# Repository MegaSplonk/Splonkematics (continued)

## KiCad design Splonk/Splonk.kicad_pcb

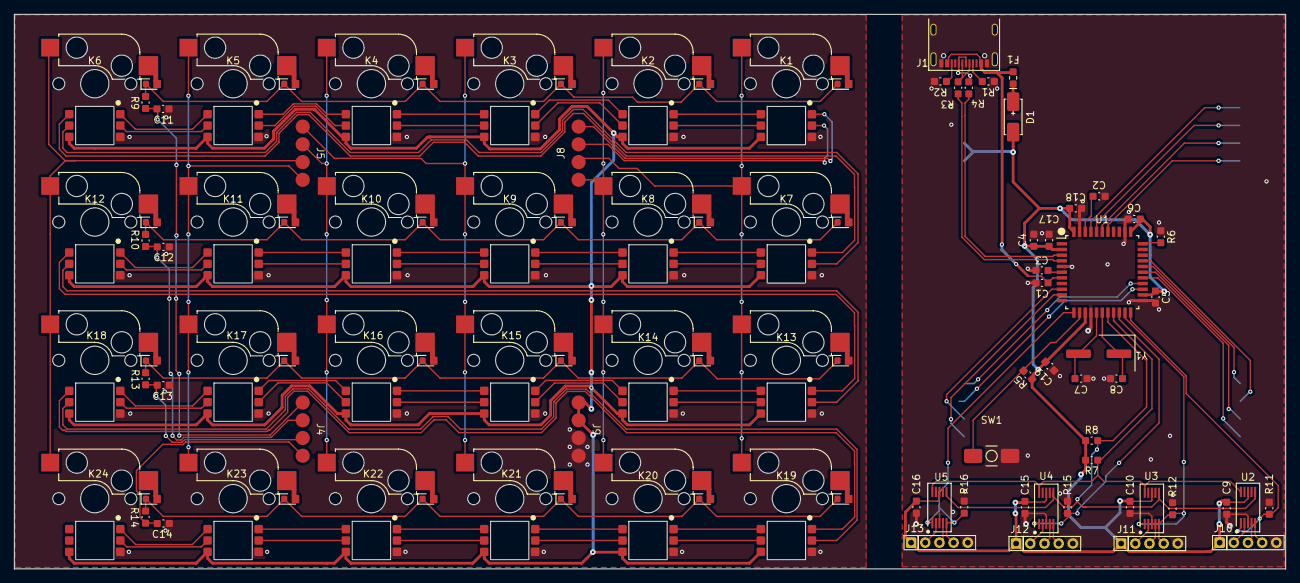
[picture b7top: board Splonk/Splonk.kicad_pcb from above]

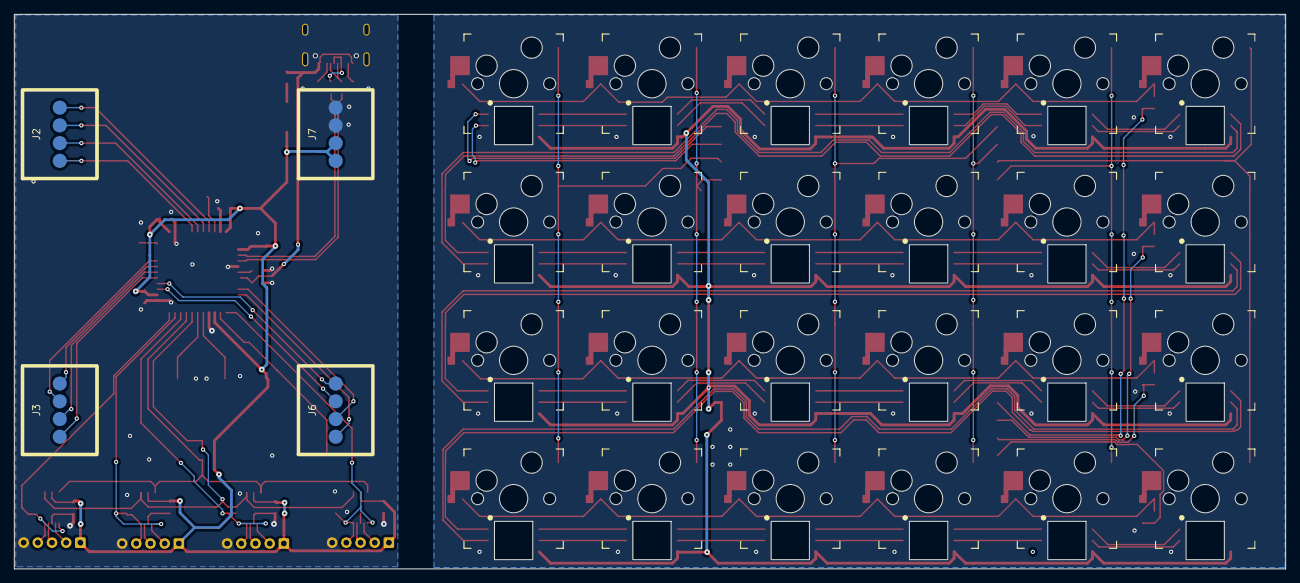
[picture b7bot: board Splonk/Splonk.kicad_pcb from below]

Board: 2 copper layers, 179.2 x 78.2 mm, 81 parts (4 on the bottom side), 104 nets.

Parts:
C1, C3, C4: 1uF; Capacitor_0603
C2, C5, C9, C10, C15, C16, C17, C18, C19: 100nF; Capacitor_0603
C6, C11, C12, C13, C14: 10uF; Capacitor_0603
C7, C8: 27pF; Capacitor_0603
D1: Diode_Schottky; Schottky
F1: PolyFuse; Diode_0603
J1: USB_C_Receptacle_USB2.0_14P; USB-C
J2, J3, J6, J7: POGO; Pogo_4_pin
J4, J5, J8, J9: POGO; Pogo_4_pin_female
J10, J11, J12, J13: SplonkConn; MaixCon-5P
K1, K2, K3, K4, K5, K6, K7, K8, K9, K10, K11, K12, K13, K14, K15, K16, K17, K18, K19, K20, K21, K22, K23, K24: APA102; Kailh_socket_MX_APA102_combo
R1, R2, R3, R4: 5.1K; Resistor_0603
R5, R6, R9, R10, R11, R12, R13, R14, R15, R16: 10K; Resistor_0603
R7, R8: 4.7K; Resistor_0603
SW1: SW_Reset; SMD_Button
U1: ATmega32U4-A; TQFP-44_10x10_Pitch0.8mm
U2, U3, U4, U5: TS5A23157; MSOP-10
Y1: 16MHz; Quatz_16Mhz

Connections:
/logic/AREF: C2.1, U1.42 (AREF)
/logic/BUS_ENABLE^{1}: J10.4, R11.1, U1.22 (PD5/XCK/~CTS), U2.1, U2.5
/logic/BUS_ENABLE^{2}: J11.4, R12.1, U1.21 (PD3/TXD1), U3.1, U3.5
/logic/BUS_ENABLE^{3}: J12.4, R15.1, U1.20 (PD2/RXD1), U4.1, U4.5
/logic/BUS_ENABLE^{4}: J13.4, R16.1, U1.12 (PB7/OC0A/OC1C/~RTS), U5.1, U5.5
/logic/COL^{1}: J6.3, U1.25 (PD4/ICP1/ADC8)
/logic/COL^{2}: J6.4, U1.26 (PD6/T1/~OC4D/ADC9)
/logic/COL^{3}: J3.1, U1.27 (PD7/T2/OC4D/ADC10)
/logic/COL^{4}: J3.2, U1.28 (PB4/ADC11)
/logic/COL^{5}: J3.4, U1.29 (PB5/ADC12/OC1A/~OC4B)
/logic/COL^{6}: J3.3, U1.30 (PB6/ADC13/OC1B/OC4B)
/logic/D+: R4.2, U1.3 (D^{+})
/logic/D-: R3.2, U1.4 (D^{-})
/logic/MOSI: J6.1, U1.10 (PB2/MOSI)
/logic/ROW^{1}: J2.1, U1.38 (PF5/ADC5)
/logic/ROW^{2}: J2.2, U1.39 (PF4/ADC4)
/logic/ROW^{3}: J2.3, U1.40 (PF1/ADC1)
/logic/ROW^{4}: J2.4, U1.41 (PF0/ADC0)
/logic/SCL: R8.2, U1.18 (PD0/OC0B/SCL), U2.6, U3.6, U4.6, U5.6
/logic/SCLK: J6.2, U1.9 (PB1/SCLK)
/logic/SDA: R7.2, U1.19 (PD1/SDA), U2.10, U3.10, U4.10, U5.10
/logic/UCAP: C3.1, U1.6 (UCap)
/logic/VUSB: C1.1, F1.1, J1.A4 (VBUS), J1.B4 (VBUS), U1.7 (VBus)
/logic/~HWB: R6.2, U1.33 (PE2/~HWB)
/logic/~RST: R5.2, SW1.1, U1.13 (~RESET)
/matrix/COL_1: J8.2, K1.7, K7.7, K13.7, K19.7
/matrix/COL_2: J8.1, K2.7, K8.7, K14.7, K20.7
/matrix/COL_3: J5.1, K3.7, K9.7, K15.7, K21.7
/matrix/COL_4: J5.2, K4.7, K10.7, K16.7, K22.7
/matrix/COL_5: J5.4, K5.7, K11.7, K17.7, K23.7
/matrix/COL_6: J5.3, K6.7, K12.7, K18.7, K24.7
/matrix/MOSI: J8.4, K1.1 (D^{in})
/matrix/R1: K1.8, K2.8, K3.8, K4.8, K5.8, K6.8, R9.1
/matrix/R2: K7.8, K8.8, K9.8, K10.8, K11.8, K12.8, R10.1
/matrix/R3: K13.8, K14.8, K15.8, K16.8, K17.8, K18.8, R13.1
/matrix/R4: K19.8, K20.8, K21.8, K22.8, K23.8, K24.8, R14.1
/matrix/ROW_1: C11.1, J4.1, R9.2
/matrix/ROW_2: C12.1, J4.2, R10.2
/matrix/ROW_3: C13.1, J4.3, R13.2
/matrix/ROW_4: C14.1, J4.4, R14.2
/matrix/SCLK: J8.3, K1.2 (C^{in})
GND: C1.2, C2.2, C3.2, C4.2, C5.2, C6.2, C7.1, C8.2, C9.1, C10.1, C11.2, C12.2, C13.2, C14.2, C15.1, C16.1, C17.2, C18.2, C19.2, J1.A1 (GND), J1.B1 (GND), J1.SH (SHIELD), J7.3, J7.4, J9.3, J9.4, J10.5, J11.5, J12.5, J13.5, K1.3 (GND), K2.3 (GND), K3.3 (GND), K4.3 (GND), K5.3 (GND), K6.3 (GND), K7.3 (GND), K8.3 (GND), K9.3 (GND), K10.3 (GND), K11.3 (GND), K12.3 (GND), K13.3 (GND), K14.3 (GND), K15.3 (GND), K16.3 (GND), K17.3 (GND), K18.3 (GND), K19.3 (GND), K20.3 (GND), K21.3 (GND), K22.3 (GND), K23.3 (GND), K24.3 (GND), R1.2, R2.2, R6.1, R11.2, R12.2, R15.2, R16.2, SW1.2, U1.5 (UGnd), U1.15 (GND), U1.23 (GND), U1.35 (GND), U1.43 (GND), U2.3 (GND), U3.3 (GND), U4.3 (GND), U5.3 (GND)
unnamed: D1.2, F1.2
unnamed: J1.A5 (CC1), R1.1
unnamed: J1.B5 (CC2), R2.1
unnamed: J1.A6 (D+), J1.B6 (D+), R4.1
unnamed: J1.A7 (D-), J1.B7 (D-), R3.1
unnamed: J10.2, U2.2
unnamed: J10.3, U2.4
unnamed: J11.2, U3.2
unnamed: J11.3, U3.4
unnamed: J12.2, U4.2
unnamed: J12.3, U4.4
unnamed: J13.2, U5.2
unnamed: J13.3, U5.4
unnamed: K1.5 (C^{out}), K2.2 (C^{in})
unnamed: K1.6 (D^{out}), K2.1 (D^{in})
unnamed: K2.5 (C^{out}), K3.2 (C^{in})
unnamed: K2.6 (D^{out}), K3.1 (D^{in})
unnamed: K3.5 (C^{out}), K4.2 (C^{in})
unnamed: K3.6 (D^{out}), K4.1 (D^{in})
unnamed: K4.5 (C^{out}), K5.2 (C^{in})
unnamed: K4.6 (D^{out}), K5.1 (D^{in})
unnamed: K5.5 (C^{out}), K6.2 (C^{in})
unnamed: K5.6 (D^{out}), K6.1 (D^{in})
unnamed: K6.5 (C^{out}), K7.2 (C^{in})
unnamed: K6.6 (D^{out}), K7.1 (D^{in})
unnamed: K7.5 (C^{out}), K8.2 (C^{in})
unnamed: K7.6 (D^{out}), K8.1 (D^{in})
unnamed: K8.5 (C^{out}), K9.2 (C^{in})
unnamed: K8.6 (D^{out}), K9.1 (D^{in})
unnamed: K9.5 (C^{out}), K10.2 (C^{in})
unnamed: K10.5 (C^{out}), K11.2 (C^{in})
unnamed: K9.6 (D^{out}), K10.1 (D^{in})
unnamed: K10.6 (D^{out}), K11.1 (D^{in})
unnamed: K11.5 (C^{out}), K12.2 (C^{in})
unnamed: K11.6 (D^{out}), K12.1 (D^{in})
unnamed: K12.5 (C^{out}), K13.2 (C^{in})
unnamed: K12.6 (D^{out}), K13.1 (D^{in})
unnamed: K13.5 (C^{out}), K14.2 (C^{in})
unnamed: K13.6 (D^{out}), K14.1 (D^{in})
unnamed: K14.5 (C^{out}), K15.2 (C^{in})
unnamed: K14.6 (D^{out}), K15.1 (D^{in})
unnamed: K15.5 (C^{out}), K16.2 (C^{in})
unnamed: K15.6 (D^{out}), K16.1 (D^{in})
unnamed: K16.5 (C^{out}), K17.2 (C^{in})
unnamed: K16.6 (D^{out}), K17.1 (D^{in})
unnamed: K17.5 (C^{out}), K18.2 (C^{in})
unnamed: K17.6 (D^{out}), K18.1 (D^{in})
unnamed: K18.5 (C^{out}), K19.2 (C^{in})
unnamed: K18.6 (D^{out}), K19.1 (D^{in})
unnamed: K19.5 (C^{out}), K20.2 (C^{in})
unnamed: K19.6 (D^{out}), K20.1 (D^{in})
unnamed: K20.5 (C^{out}), K21.2 (C^{in})
unnamed: K20.6 (D^{out}), K21.1 (D^{in})
unnamed: K21.5 (C^{out}), K22.2 (C^{in})
unnamed: K21.6 (D^{out}), K22.1 (D^{in})
unnamed: K22.5 (C^{out}), K23.2 (C^{in})
unnamed: K22.6 (D^{out}), K23.1 (D^{in})
unnamed: K23.5 (C^{out}), K24.2 (C^{in})
unnamed: K23.6 (D^{out}), K24.1 (D^{in})
unnamed: C8.1, U1.17 (XTAL1), Y1.1
unnamed: C7.2, U1.16 (XTAL2), Y1.2
VCC: C4.1, C5.1, C6.1, C9.2, C10.2, C15.2, C16.2, C17.1, C18.1, C19.1, D1.1, J7.1, J7.2, J9.1, J9.2, J10.1, J11.1, J12.1, J13.1, K1.4 (VCC), K2.4 (VCC), K3.4 (VCC), K4.4 (VCC), K5.4 (VCC), K6.4 (VCC), K7.4 (VCC), K8.4 (VCC), K9.4 (VCC), K10.4 (VCC), K11.4 (VCC), K12.4 (VCC), K13.4 (VCC), K14.4 (VCC), K15.4 (VCC), K16.4 (VCC), K17.4 (VCC), K18.4 (VCC), K19.4 (VCC), K20.4 (VCC), K21.4 (VCC), K22.4 (VCC), K23.4 (VCC), K24.4 (VCC), R5.1, R7.1, R8.1, U1.2 (UVcc), U1.14 (VCC), U1.24 (AVCC), U1.34 (VCC), U1.44 (AVCC), U2.8 (VCC), U3.8 (VCC), U4.8 (VCC), U5.8 (VCC)

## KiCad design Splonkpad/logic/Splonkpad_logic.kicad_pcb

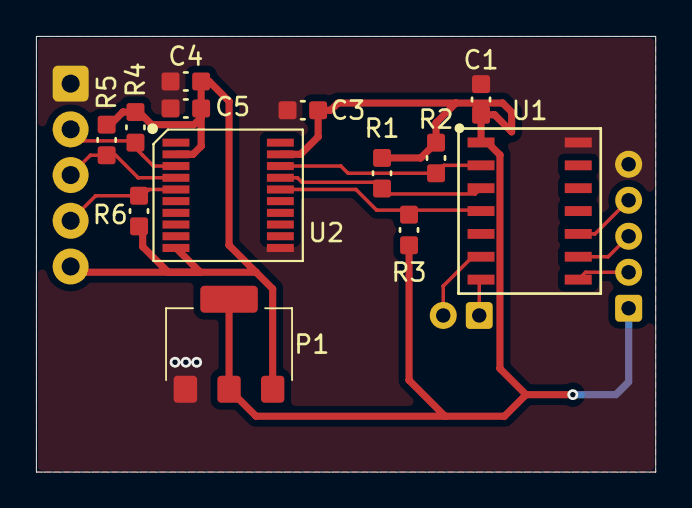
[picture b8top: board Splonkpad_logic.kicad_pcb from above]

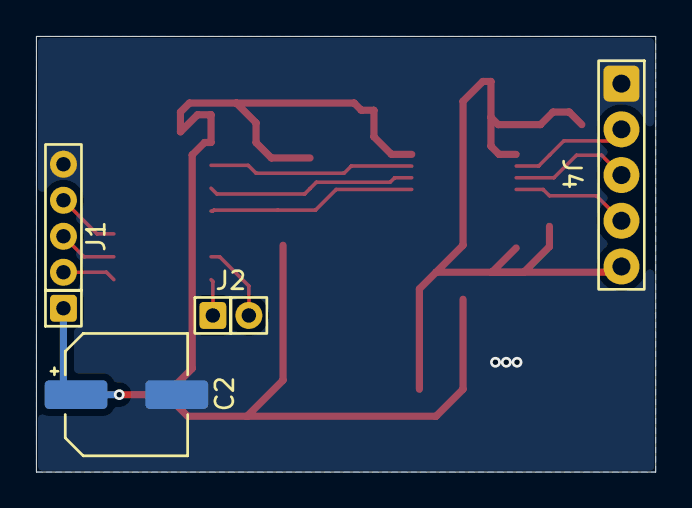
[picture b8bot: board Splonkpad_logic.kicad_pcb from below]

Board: 2 copper layers, 34.4 x 24.2 mm, 17 parts (4 on the bottom side), 14 nets.

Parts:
C1: 10nF; Capacitor_0603
C2: 100uF; ElectroliticCapacitor
C3, C4: 100nF; Capacitor_0603
C5: 10uF; Capacitor_0603
J1: SplonkConn; MaixCon-5P
J2: UART; MaixCon-2P
J4: Pad Conn; Pin_header_5
P1: AMS1117-3.3; AMS1117
R1, R2, R4, R5: 4.7K; Resistor_0603
R3, R6: 10K; Resistor_0603
U1: ATtiny1614-SS; SOIC-14
U2: TXS0108EPW; TSSOP-20

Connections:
3.3V: C4.1, C5.1, J4.5, P1.3 (V^{in}), R4.1, R5.1, R6.2, U2.2 (VCCA), U2.10 (OE)
/RX: J2.1, U1.7 (RX/PB2)
/SCL: J1.3, U1.9 (SCL/PB0)
/SCL^{3.3S}: J4.2, R4.2, U2.3 (A2)
/SDA: J1.2, U1.8 (SDA/PB1)
/SDA^{3.3S}: J4.3, R5.2, U2.4 (A3)
/TX: J2.2, U1.6 (TX/PB3)
/UPDI: J1.4, U1.10 (UPDI/PA0)
/~RST^{3.3S}: J4.4, R6.1, U2.5 (A4)
GND: C1.2, C2.-, C3.2, C4.2, C5.2, J1.5, J4.1, P1.1 (GND), U1.14 (GND), U2.11 (GND)
unnamed: R2.2, U1.2 (PA4), U2.18 (B2)
unnamed: R1.2, U1.3 (PA5), U2.17 (B3)
unnamed: R3.1, U1.4 (PA6), U2.16 (B4)
VCC: C1.1, C2.+, C3.1, J1.1, P1.2 (V^{out}), P1.4 (V^{out}), R1.1, R2.1, R3.2, U1.1 (VCC), U2.19 (VCCB)

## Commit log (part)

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2026-06-01 Added Schematic and project files
2026-06-01 Changed pins around a bit
2026-06-16 feat(splonkpad): splonkpad part of the things
